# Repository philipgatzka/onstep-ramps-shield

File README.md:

# onstep-ramps-shield

This is an add-on board for a RAMPSv1.4 (and some later versions) board, which
carries a bit of additional hardware necessary for an
[OnStep](https://github.com/hjd1964/OnStep)
telescope controller.

There are different ways to build an OnStep, including using a completely custom
board, but I liked the modular approach and used an Arduino Mega in combination
with a RAMPS shield. The custom boards of course offer places to fit connectors
and such which the Arduino/RAMPS combination doesn't, so I'm trying to build
this board to help with that.

At the moment, the board takes the following components:
- RA motor connector, RJ12 6p6c
- DEC motor connector, RJ12 6p6c
- Focuser motor 1 connector, RJ12 6p6c
- Focuser motor 2 connector, RJ12 6p6c
- (Polar alignment scope illuminator connector, 3-Pin 3.5mm audio jack)
- (PEC sensor connector, 3-Pin 3.5mm audio jack)
- Buzzer
- DS3231 RTC via I2C
- BME280 environmental sensor via I2C
- HC05 Bluetooth module via Serial

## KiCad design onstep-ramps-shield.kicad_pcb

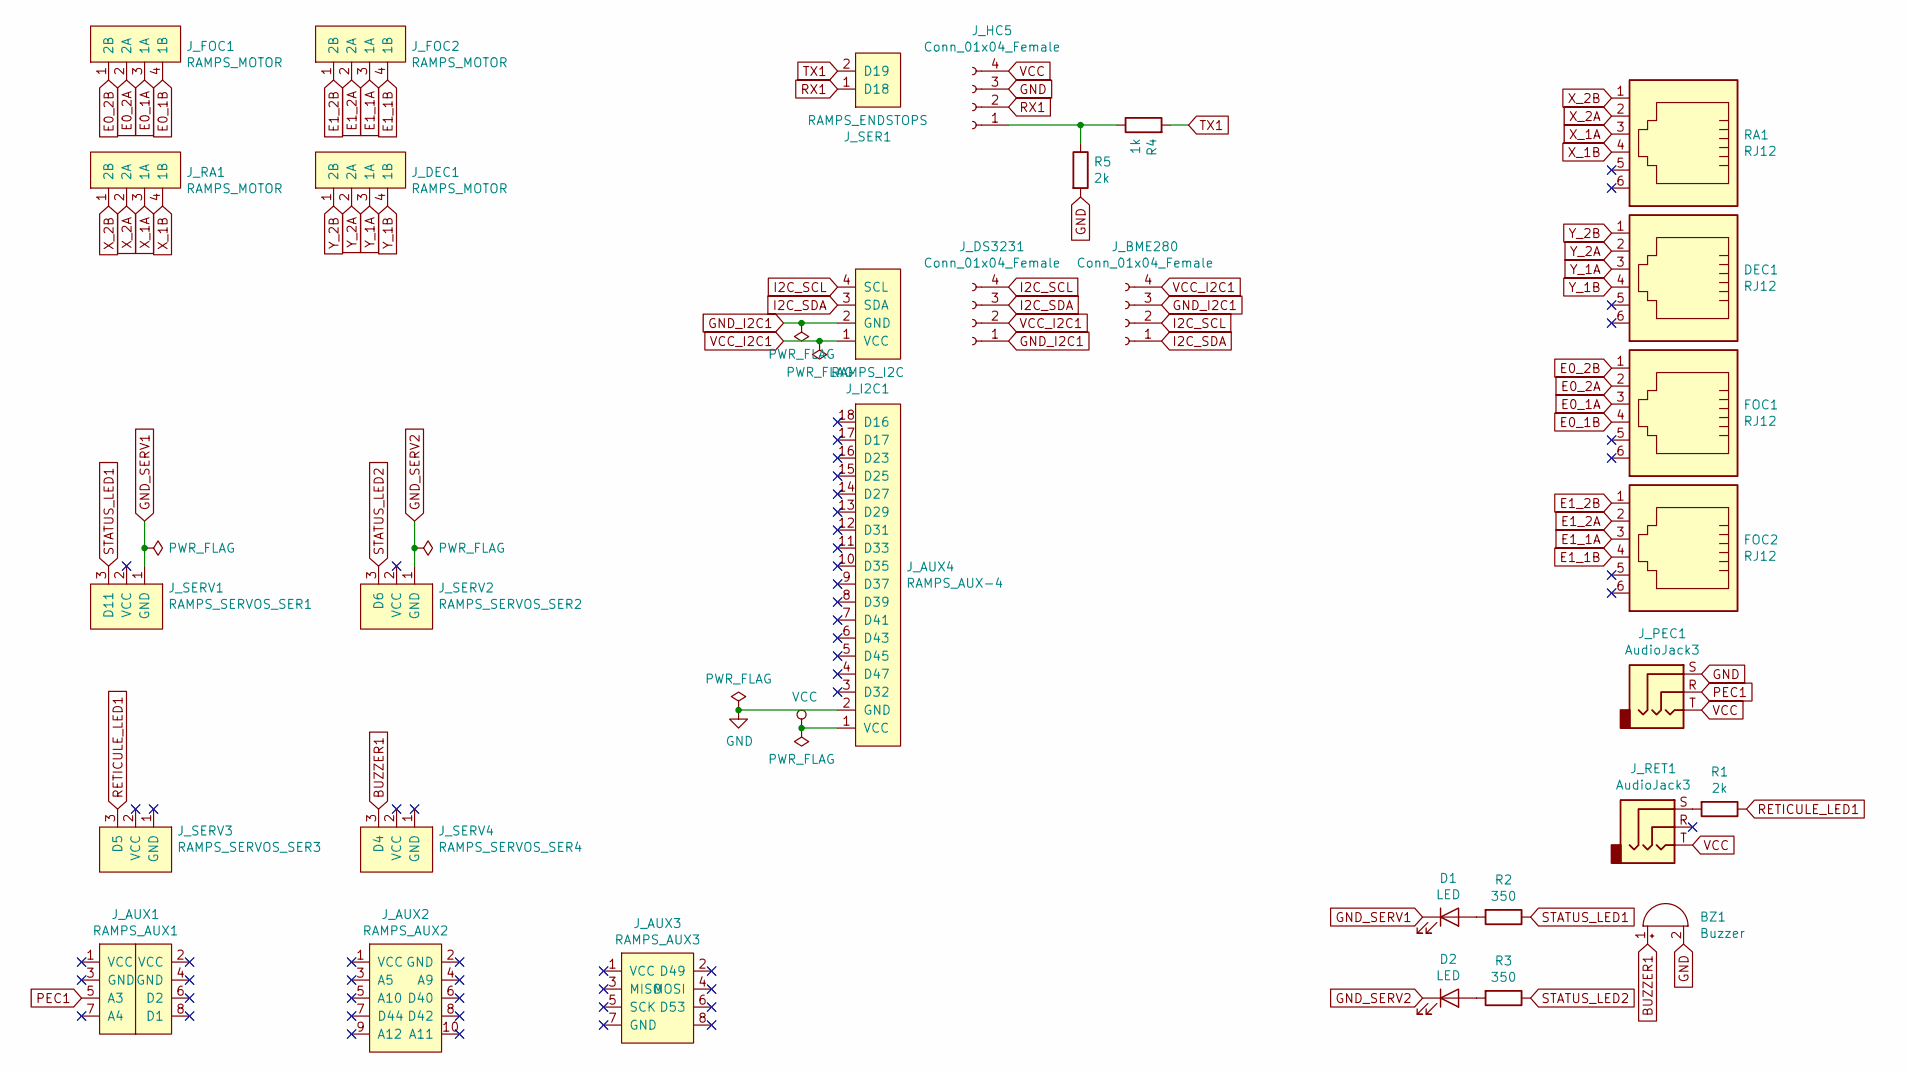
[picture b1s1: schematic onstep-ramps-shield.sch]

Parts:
BZ1: Buzzer; Buzzer_12x9.5RM7.6
D1, D2: LED; LED_0603_1608Metric_Pad1.05x0.95mm_HandSolder
DEC1: RJ12; RJ12_Amphenol_54601
FOC1, FOC2: RJ12; RJ12_Amphenol_54601
J_AUX1: RAMPS_AUX1; PinSocket_2x04_P2.54mm_Vertical
J_AUX2: RAMPS_AUX2; PinSocket_2x05_P2.54mm_Vertical
J_AUX3: RAMPS_AUX3; PinSocket_2x04_P2.54mm_Vertical
J_AUX4: RAMPS_AUX-4; PinSocket_1x18_P2.54mm_Vertical
J_BME280: Conn_01x04_Female; PinSocket_1x04_P2.54mm_Vertical
J_DEC1: RAMPS_MOTOR; PinSocket_1x04_P2.54mm_Vertical
J_DS3231: Conn_01x04_Female; PinSocket_1x04_P2.54mm_Vertical
J_FOC1, J_FOC2: RAMPS_MOTOR; PinSocket_1x04_P2.54mm_Vertical
J_HC5: Conn_01x04_Female; PinSocket_1x04_P2.54mm_Vertical
J_I2C1: RAMPS_I2C; PinSocket_1x04_P2.54mm_Vertical
J_PEC1: AudioJack3; Jack_3.5mm_CUI_SJ1-3533NG_Horizontal_CircularHoles
J_RA1: RAMPS_MOTOR; PinSocket_1x04_P2.54mm_Vertical
J_RET1: AudioJack3; Jack_3.5mm_CUI_SJ1-3533NG_Horizontal_CircularHoles
J_SER1: RAMPS_ENDSTOPS; PinSocket_1x02_P2.54mm_Vertical
J_SERV1: RAMPS_SERVOS_SER1; PinSocket_1x03_P2.54mm_Vertical
J_SERV2: RAMPS_SERVOS_SER2; PinSocket_1x03_P2.54mm_Vertical
J_SERV3: RAMPS_SERVOS_SER3; PinSocket_1x03_P2.54mm_Vertical
J_SERV4: RAMPS_SERVOS_SER4; PinSocket_1x03_P2.54mm_Vertical
R1, R5: 2k; R_0603_1608Metric_Pad1.05x0.95mm_HandSolder
R2, R3: 350; R_0603_1608Metric_Pad1.05x0.95mm_HandSolder
R4: 1k; R_0603_1608Metric_Pad1.05x0.95mm_HandSolder
RA1: RJ12; RJ12_Amphenol_54601

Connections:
BUZZER1: BZ1.1 (-), J_SERV4.3 (D4)
E0_1A: FOC1.3, J_FOC1.3 (1A)
E0_1B: FOC1.4, J_FOC1.4 (1B)
E0_2A: FOC1.2, J_FOC1.2 (2A)
E0_2B: FOC1.1, J_FOC1.1 (2B)
E1_1A: FOC2.3, J_FOC2.3 (1A)
E1_1B: FOC2.4, J_FOC2.4 (1B)
E1_2A: FOC2.2, J_FOC2.2 (2A)
E1_2B: FOC2.1, J_FOC2.1 (2B)
GND: BZ1.2 (+), J_AUX4.2 (GND), J_HC5.3, J_PEC1.S, R5.2
GND_I2C1: J_BME280.3, J_DS3231.1, J_I2C1.2 (GND)
GND_SERV1: D1.1 (K), J_SERV1.1 (GND)
GND_SERV2: D2.1 (K), J_SERV2.1 (GND)
I2C_SCL: J_BME280.2, J_DS3231.4, J_I2C1.4 (SCL)
I2C_SDA: J_BME280.1, J_DS3231.3, J_I2C1.3 (SDA)
unnamed: D1.2 (A), R2.2
unnamed: D2.2 (A), R3.2
unnamed: J_HC5.1, R4.1, R5.1
unnamed: J_RET1.S, R1.2
PEC1: J_AUX1.5 (A3), J_PEC1.R
RETICULE_LED1: J_SERV3.3 (D5), R1.1
RX1: J_HC5.2, J_SER1.1 (D18)
STATUS_LED1: J_SERV1.3 (D11), R2.1
STATUS_LED2: J_SERV2.3 (D6), R3.1
TX1: J_SER1.2 (D19), R4.2
VCC: J_AUX4.1 (VCC), J_HC5.4, J_PEC1.T, J_RET1.T
VCC_I2C1: J_BME280.4, J_DS3231.2, J_I2C1.1 (VCC)
X_1A: J_RA1.3 (1A), RA1.3
X_1B: J_RA1.4 (1B), RA1.4
X_2A: J_RA1.2 (2A), RA1.2
X_2B: J_RA1.1 (2B), RA1.1
Y_1A: DEC1.3, J_DEC1.3 (1A)
Y_1B: DEC1.4, J_DEC1.4 (1B)
Y_2A: DEC1.2, J_DEC1.2 (2A)
Y_2B: DEC1.1, J_DEC1.1 (2B)

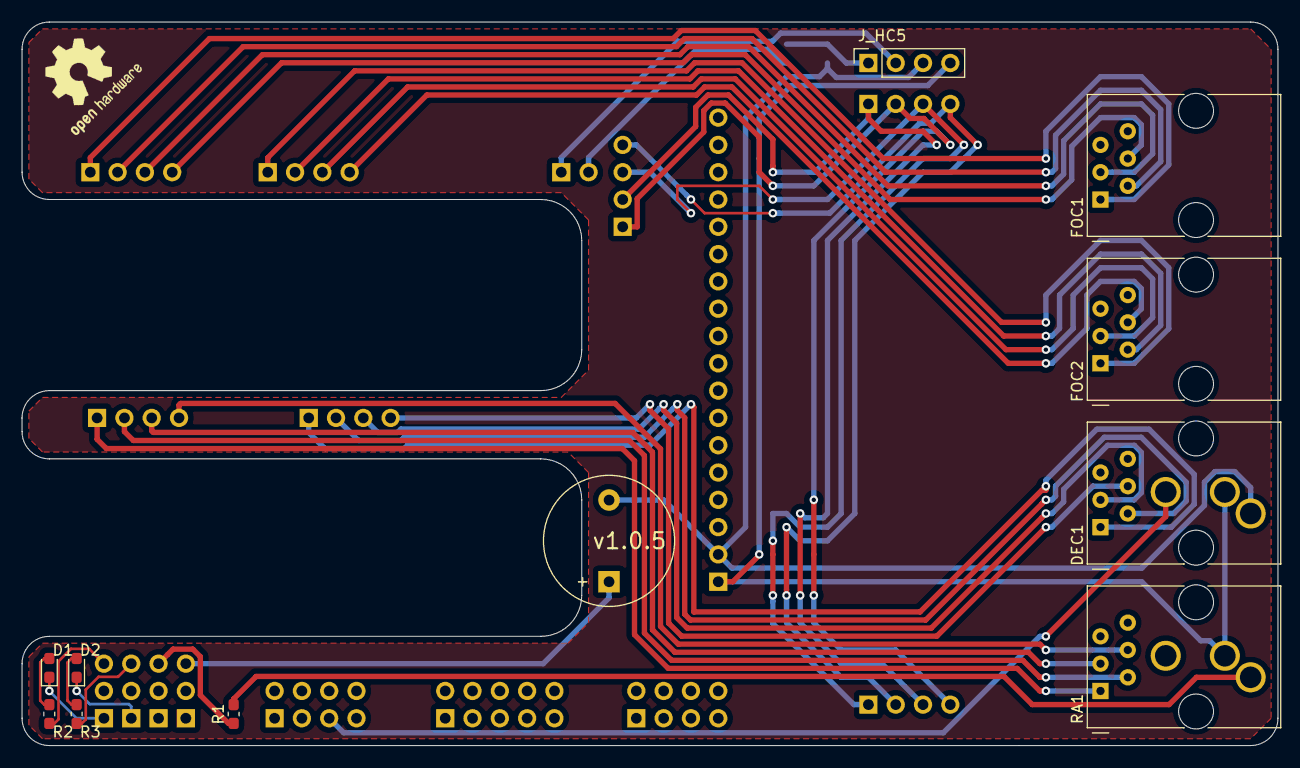
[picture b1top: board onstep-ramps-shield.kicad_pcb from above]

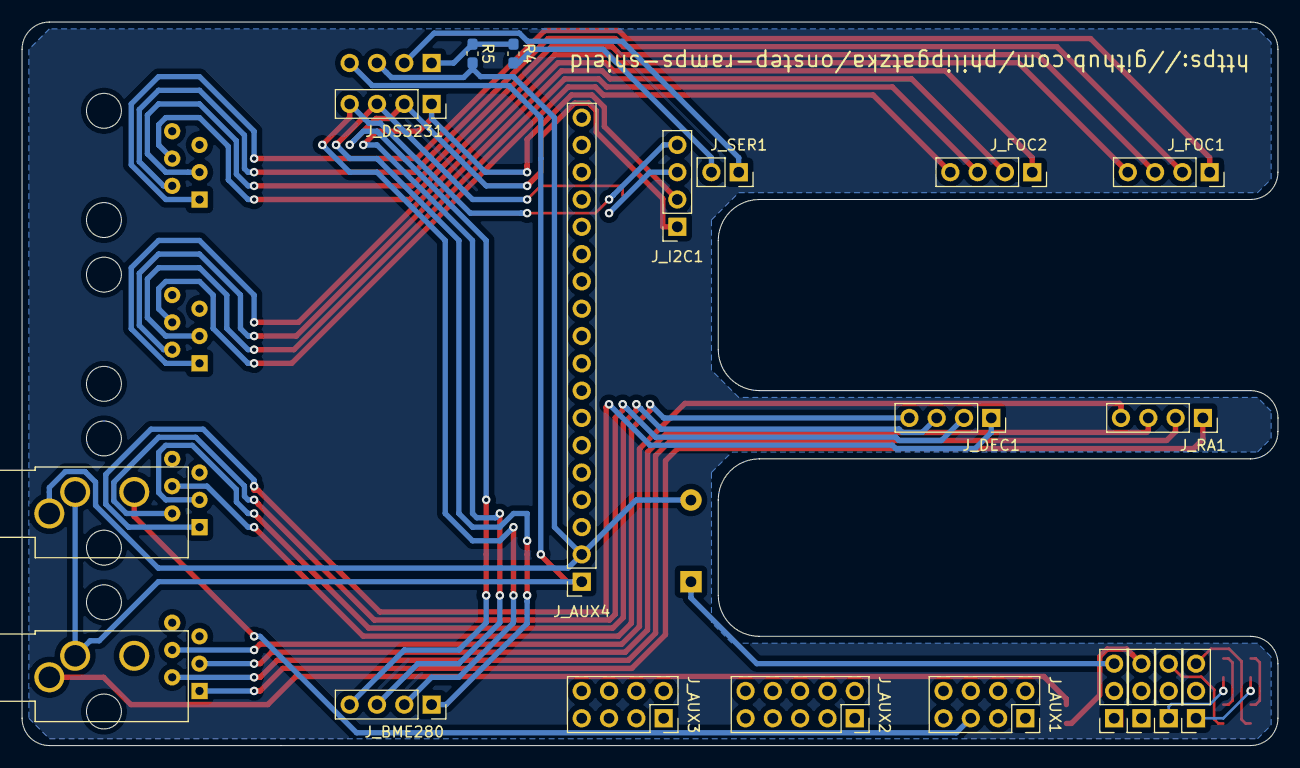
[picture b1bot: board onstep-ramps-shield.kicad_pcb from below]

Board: 2 copper layers, 116.8 x 67.3 mm, 31 parts (20 on the bottom side), 35 nets.

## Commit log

2020-08-31 KiCad init
2020-08-31 Add RAMPS connectors to project library
2020-08-31 Schematic, initial board layout
2020-08-31 WIP - Routing
2020-09-02 Routing
2020-09-03 Include HC05
2020-09-05 Measured distances
2020-09-05 Reorder components
2020-09-05 Copper fill
2020-09-05 Gerbers
2020-09-05 Increase inner corner radius
2020-09-05 Remove gerbers
2020-09-05 Add .gitignore for gerber files
2020-09-05 Update connectors
2020-09-05 Add voltage divider for HC05
2020-09-05 Re-route R4 trace
2020-09-05 Rearrange resistors
2020-09-05 Screenshot
2020-09-06 Increase trace to edge distance for LEDs
2020-09-17 Increased connector distance
2020-09-17 Add silkscreen version info
2020-09-17 Scale down
2020-10-01 Update distances
2022-01-12 Update .gitignore files
